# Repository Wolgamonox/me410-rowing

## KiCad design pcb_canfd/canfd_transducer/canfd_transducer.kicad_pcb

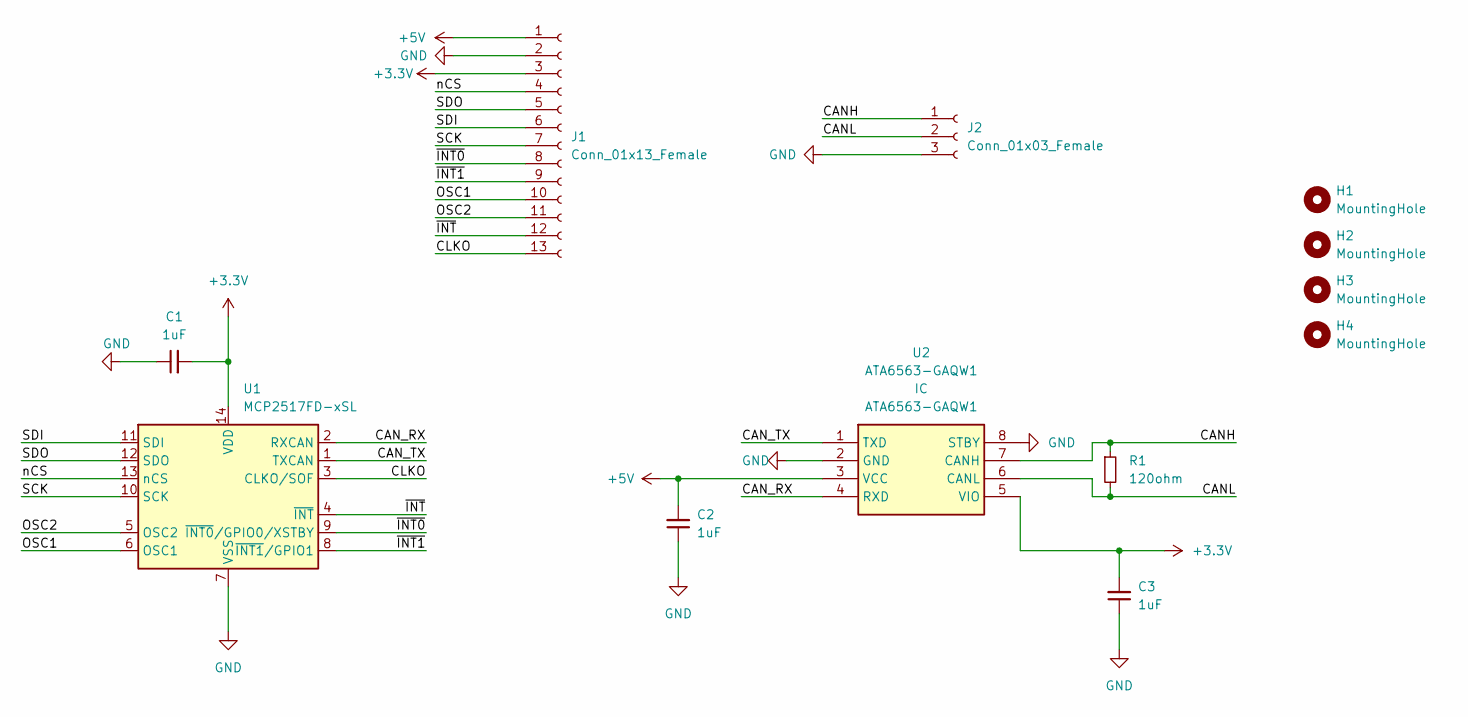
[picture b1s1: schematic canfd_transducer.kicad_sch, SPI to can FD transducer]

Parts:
C1, C2, C3: 1uF; C_0603_1608Metric
H1, H2, H3, H4: MountingHole; MountingHole_3.2mm_M3_DIN965_Pad_TopOnly
J1: Conn_01x13_Female; PinSocket_1x13_P2.54mm_Vertical
J2: Conn_01x03_Female; JST_PH_B3B-PH-K_1x03_P2.00mm_Vertical
R1: 120ohm; R_0805_2012Metric
U1: MCP2517FD-xSL; SOIC-14_3.9x8.7mm_P1.27mm
U2: ATA6563-GAQW1; SOIC127P600X175-8N; Mouser Part Number 579-ATA6563-GAQW1

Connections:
+3.3V: C1.2, C3.2, J1.3, U1.14 (VDD), U2.5 (VIO)
+5V: C2.2, J1.1, U2.3 (VCC)
/CANH: J2.1, R1.1, U2.7 (CANH)
/CANL: J2.2, R1.2, U2.6 (CANL)
/CAN_RX: U1.2 (RXCAN), U2.4 (RXD)
/CAN_TX: U1.1 (TXCAN), U2.1 (TXD)
/CLKO: J1.13, U1.3 (CLKO/SOF)
/OSC1: J1.10, U1.6 (OSC1)
/OSC2: J1.11, U1.5 (OSC2)
/SCK: J1.7, U1.10 (SCK)
/SDI: J1.6, U1.11 (SDI)
/SDO: J1.5, U1.12 (SDO)
/nCS: J1.4, U1.13 (nCS)
/~INT0: J1.8, U1.9 (~INT0/GPIO0/XSTBY)
/~INT1: J1.9, U1.8 (~INT1/GPIO1)
/~INT: J1.12, U1.4 (~INT)
GND: C1.1, C2.1, C3.1, J1.2, J2.3, U1.7 (VSS), U2.2 (GND), U2.8 (STBY)

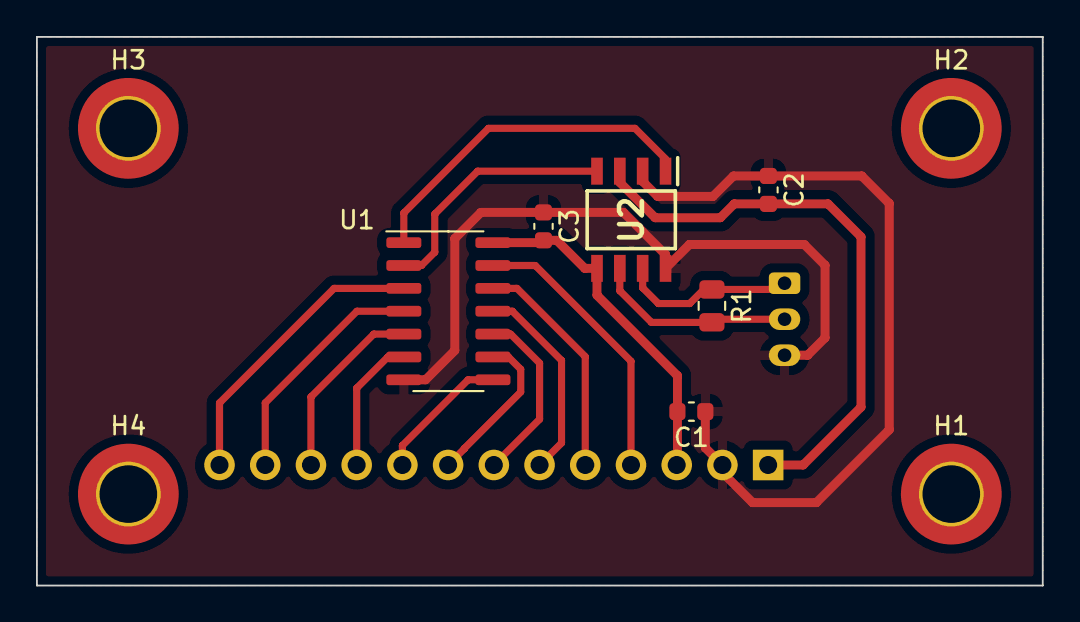
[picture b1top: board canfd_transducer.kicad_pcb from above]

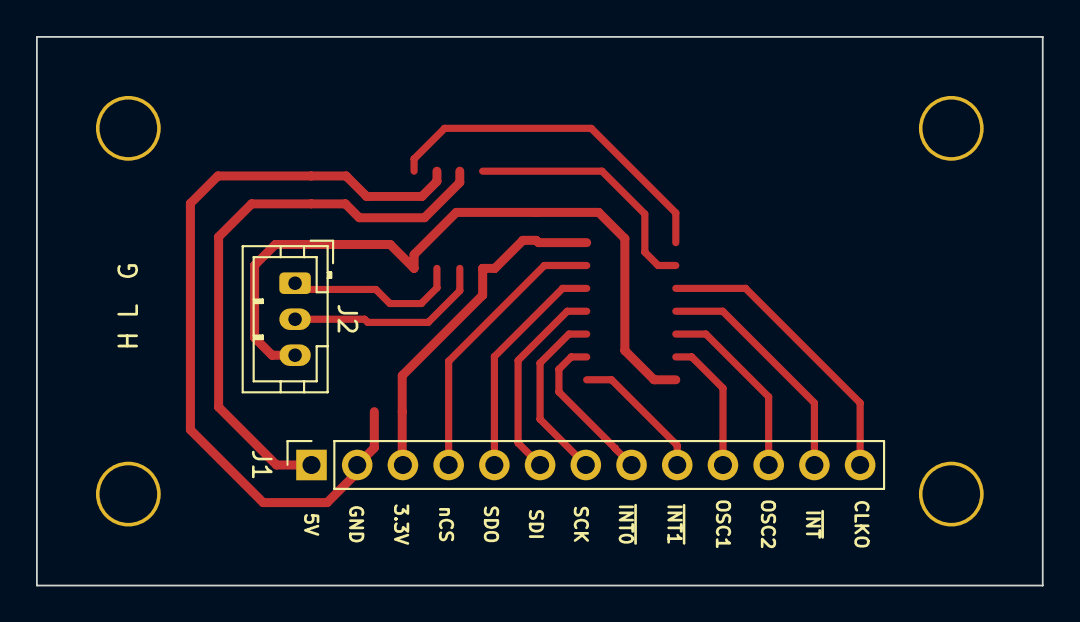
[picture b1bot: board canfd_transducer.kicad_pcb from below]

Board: 2 copper layers, 55.9 x 30.5 mm, 12 parts (2 on the bottom side), 17 nets.

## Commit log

2023-10-19 initial commit + first draft of button
2023-10-19 added working principle diagram
2023-10-21 started working on PCB for FDCAN transducer
2023-10-21 finished first version of board, needs revision
2023-10-21 added epfl lab capabilities pdf
2023-10-23 small changes
2023-10-23 added backups
2023-10-28 added bluetooth tests
2023-10-28 added resistor for can bus
2023-10-28 started leader ble loop
2023-10-28 started follower loop, crashes
2023-10-29 working follower loop
2023-10-29 bluetooth communication works !
2023-11-02 Working first loop with buttons and leds !
2023-11-05 prop change
2023-11-05 added esp start
2023-11-07 added comments
2023-11-08 continue interface
2023-11-08 working ESP NOW !!
2023-11-09 started I2C
2023-11-12 started I2C comm
2023-11-12 Working wired comm, need to clean the code
2023-11-15 Added example of working loopback for ESP <=> CAN
2023-11-16 changed frequency to 20Mhz
2023-11-20 started electronics schematics
2023-11-20 working motor control
2023-11-21 add mteus
2023-11-21 added encoder + moteus
2023-11-22 leds + user interface
2023-11-22 add core_juju
2023-11-22 re added core
2023-11-22 Add motor control + encoder
2023-11-24 file cleanup
2023-11-24 added complete circuit electronics
2023-11-24 refactoring of print statements
2023-11-24 added sounds
2023-11-24 started monitoring script
2023-11-28 changed setleds back
2023-11-28 added beep
2023-11-28 added new mac address
2023-11-28 solved bug
2023-11-30 changed can frequency to 40
2023-11-30 changed motor id
2023-11-30 added verbosity levels
2023-11-30 changed pins and configuration
2023-11-30 minor udpate
2023-11-30 added calibration step working but with offset
2023-11-30 working movement
2023-11-30 cleanup
2023-11-30 added experiment 1 analysis
2023-12-01 kinda better delay graph and a bit of tuning
2023-12-02 added filtering to the graphs
2023-12-02 added new diagram
2023-12-02 added filter to analysis
2023-12-05 add simultaneous plot for leader and follower
2023-12-06 working real time plot + add Ki + change address
2023-12-07 modified looks of electronics
2023-12-08 fixed wired communication
2023-12-08 removed -1
2023-12-13 added communication class diagram
2023-12-13 changed code for frequency analysis
2023-12-14 added frequency analysis results
